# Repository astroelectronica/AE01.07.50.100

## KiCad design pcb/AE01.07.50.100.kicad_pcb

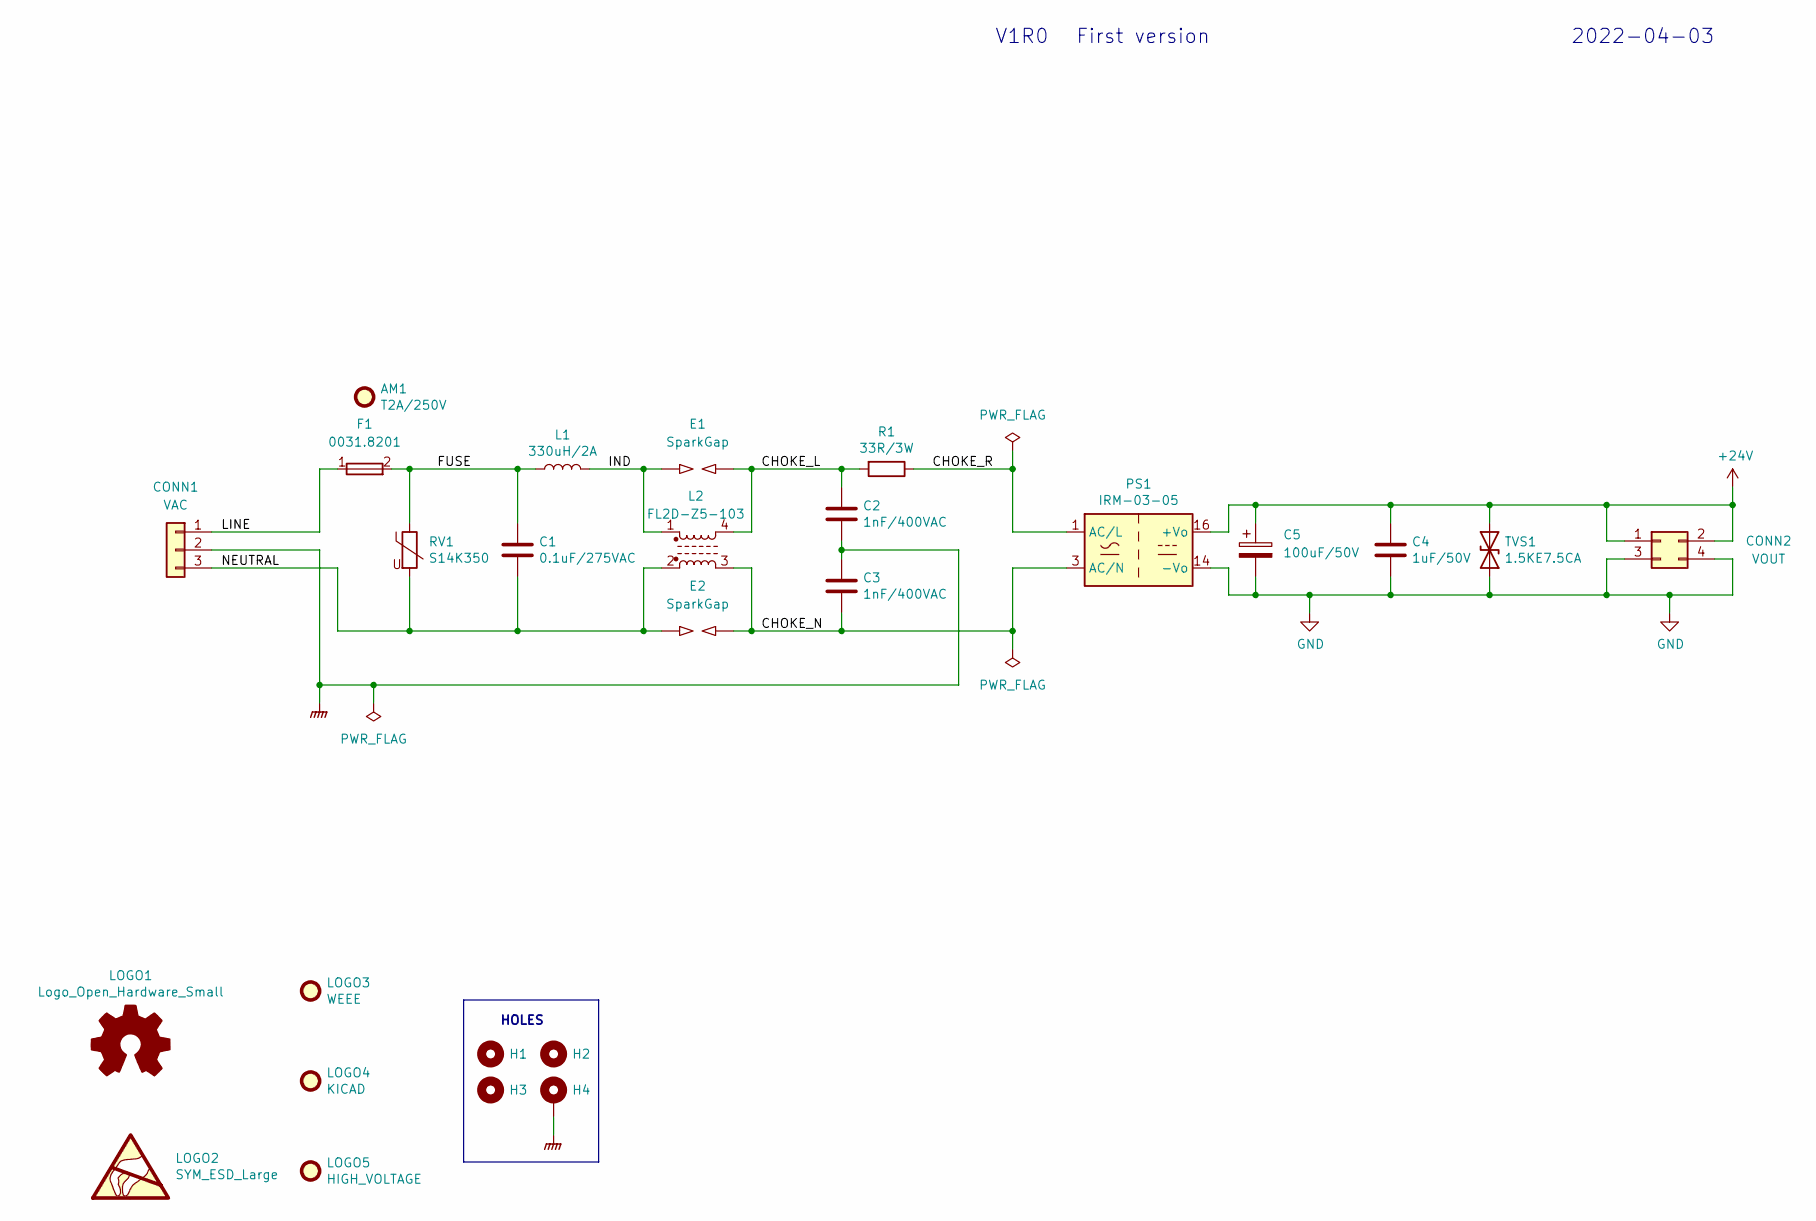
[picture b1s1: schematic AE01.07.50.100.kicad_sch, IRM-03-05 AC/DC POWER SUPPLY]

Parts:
AM1: T2A/250V; -; MPN 0034.3120
C1: 0.1uF/275VAC; C_Rect_L18.0mm_W5.0mm_P15.00mm_FKS3_FKP3; MPN R46KI310000M1M
C2, C3: 1nF/400VAC; C_Disc_D7.5mm_W5.0mm_P7.50mm; MPN CS65ZU2GA102MANKA
C4: 1uF/50V; C_Disc_D5.1mm_W3.2mm_P5.00mm; MPN K105M20X7RF53H5
C5: 100uF/50V; CP_Radial_D8.0mm_P3.50mm; MPN UPW1J680MPD1TD
CONN1: VAC; TerminalBlock_Phoenix_MKDS-1,5-3-5.08_1x03_P5.08mm_Horizont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; MPN 1715857
CONN2: VOUT; PinSocket_2x02_P2.54mm_Vertical; MPN BCS-101-L-D-TE
E1, E2: SparkGap; SparkGap-2_P1.3mm_OpenTrianglePad1.0x1.5mm; MPN NO_BOM
F1: 0031.8201; Fuseholder_Cylinder-5x20mm_Schurter_0031_8201_Horizontal_Op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; MPN 0031.8201
H1, H2, H3: MountingHole; MountingHole_3.2mm_M3; MPN NO_BOM
H4: MountingHole_Pad; MountingHole_3.2mm_M3_Pad_Via; MPN NO_BOM
L1: 330uH/2A; L_Toroid_Vertical_L25.4mm_W14.7mm_P12.20mm_Vishay_TJ5_BigPa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; MPN DPO-3.0-330
L2: FL2D-Z5-103; MPN FL2D-Z5-103
LOGO1: Logo_Open_Hardware_Small; OSHW-Logo_5.7x6mm_SilkScreen; MPN NO_BOM
LOGO2: SYM_ESD_Large; ESD-Logo_6.6x6mm_SilkScreen; MPN NO_BOM
LOGO3: WEEE; WEEE-Logo_4.2x6mm_SilkScreen; MPN NO_BOM
LOGO4: KICAD; KiCad-Logo2_5mm_SilkScreen; MPN NO_BOM
LOGO5: HIGH_VOLTAGE; Symbol_HighVoltage_Type2_CopperTop_VerySmall; MPN NO_BOM
PS1: IRM-03-05; Converter_ACDC_MeanWell_IRM-03-xx_THT; MPN IRM-03-05
R1: 33R/3W; R_Axial_DIN0516_L15.5mm_D5.0mm_P5.08mm_Vertical; MPN ROX3SJ33R
RV1: S14K350; RV_Disc_D15.5mm_W3.9mm_P7.5mm; MPN B72214P2351K101
TVS1: 1.5KE7.5CA; D_DO-201_P5.08mm_Vertical_KathodeUp; MPN 1.5KE7.5CA

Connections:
+24V: C4.1, C5.1, CONN2.1, CONN2.2, PS1.16 (+Vo), TVS1.1 (A1)
/CHOKE_L: C2.1, E1.2, L2.4, R1.2
/CHOKE_N: C3.2, E2.2, L2.3, PS1.3 (AC/N)
/CHOKE_R: PS1.1 (AC/L), R1.1
/FUSE: C1.1, F1.2, L1.1, RV1.1
/IND: E1.1, L1.2, L2.1
/LINE: CONN1.1, F1.1
/NEUTRAL: C1.2, CONN1.3, E2.1, L2.2, RV1.2
GND: C4.2, C5.2, CONN2.3, CONN2.4, PS1.14 (-Vo), TVS1.2 (A2)
GNDPWR: C2.2, C3.1, CONN1.2, H4.1

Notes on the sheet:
HOLES
2022-04-03
First version
V1R0

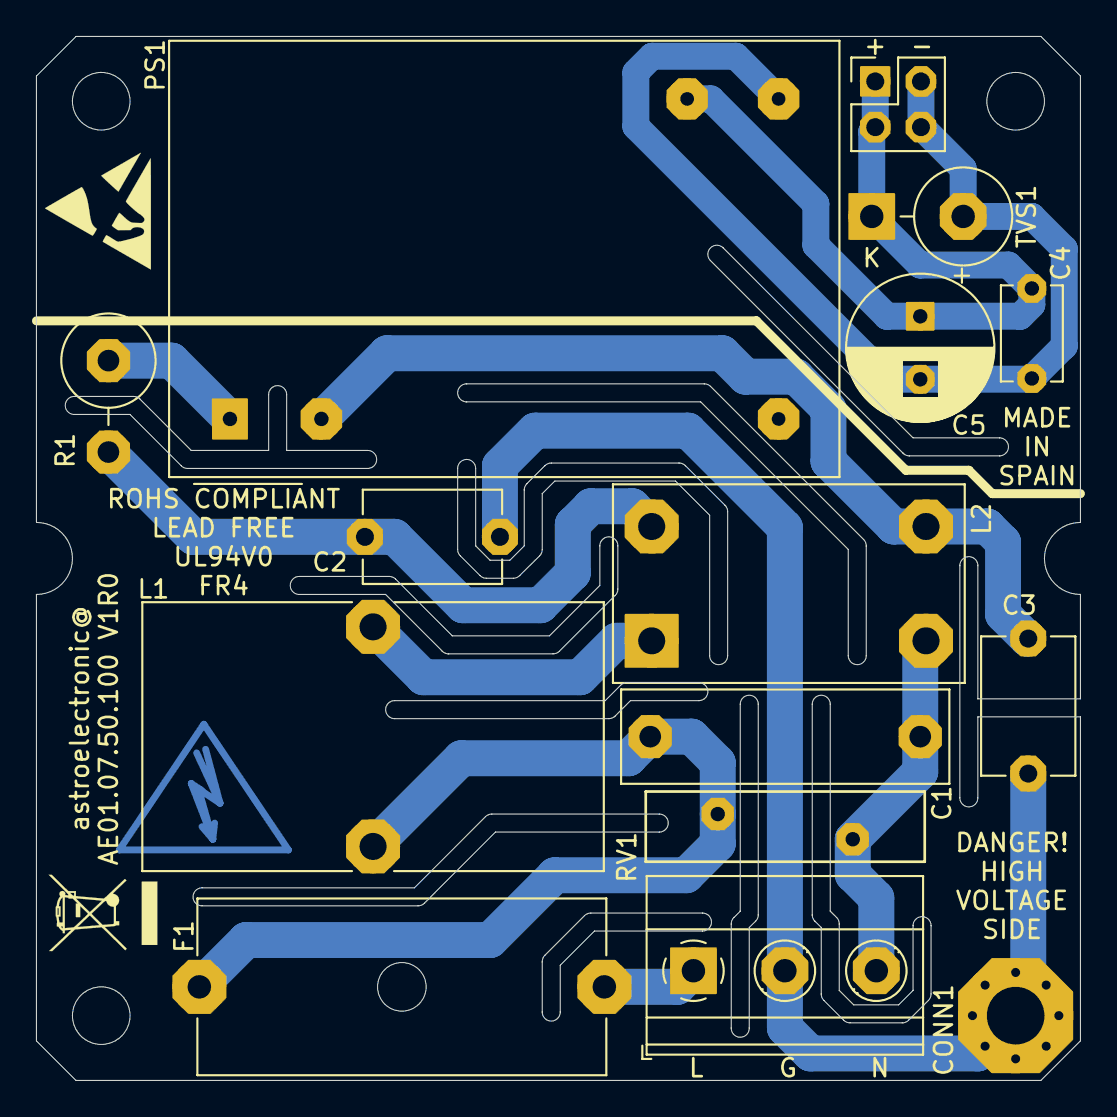
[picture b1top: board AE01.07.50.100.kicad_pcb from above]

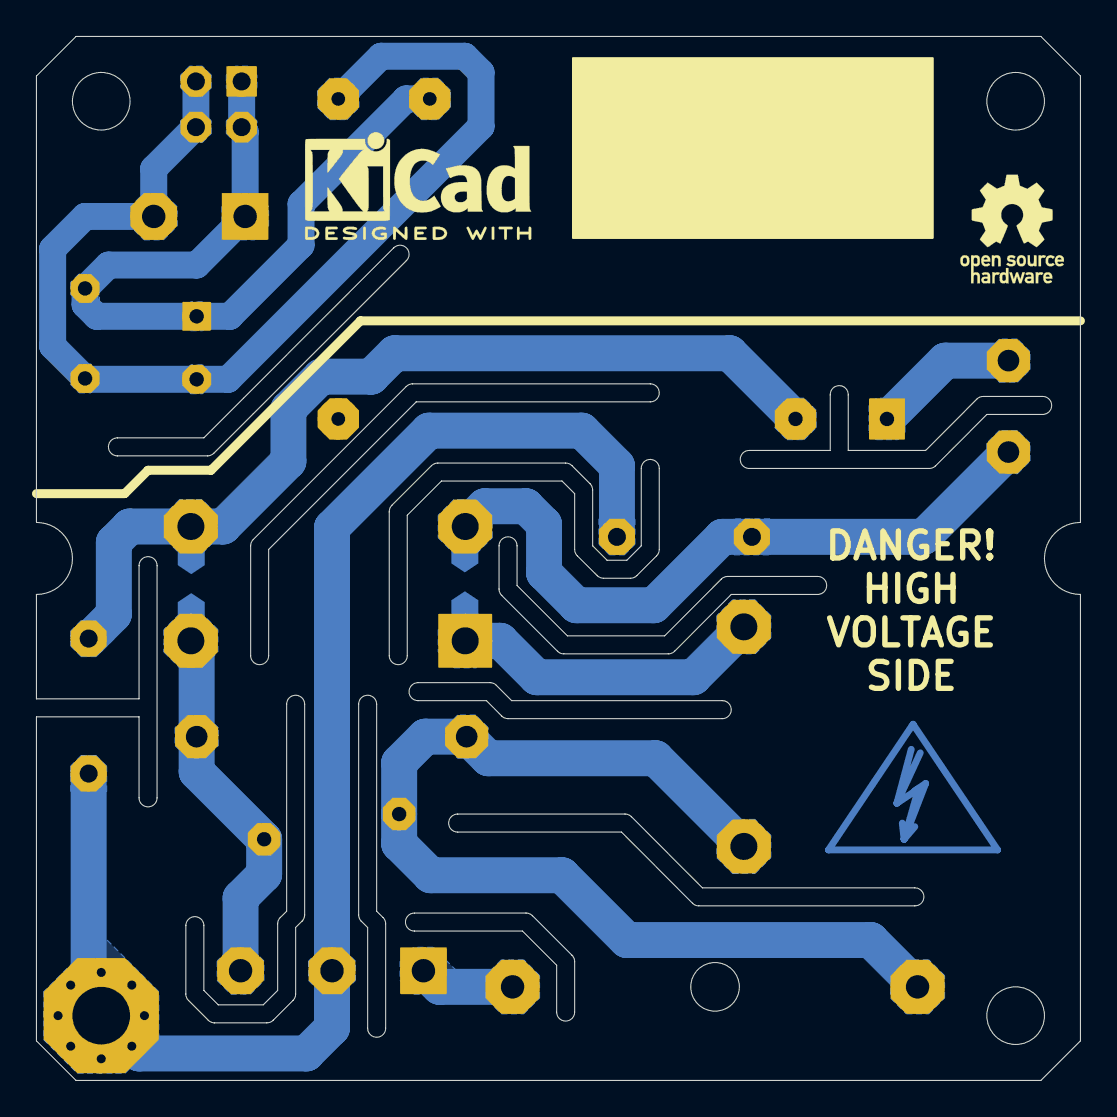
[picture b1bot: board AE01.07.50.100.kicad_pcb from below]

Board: 2 copper layers, 58.0 x 58.0 mm, 25 parts (5 on the bottom side), 10 nets.

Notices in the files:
pcb/AE01.07.50.100.kicad_pcb:
CC BY-SA
